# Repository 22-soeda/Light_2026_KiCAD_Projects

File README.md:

2026 ３月のROBO-ONE light 向けの回路CAD

工大祭(2025 11月頭)に向けて
 - main esp32e can
   - esp32とPCをwifiで接続して、GUIでロボットをデバッグ
   - Serial2をTTL変換して、zhコネクタで6ポート出力
   - 7.4VDCDC,12V 強電の系をまとめてスイッチング
   - canを2ポート搭載
   - 終端抵抗はブリッジで選択
   - BNO055はUART(Serial1)で実装
   - 5V reg, 3.3V DCDCを搭載
 - FSR to can
   - ATmega328P-AUをマイコンとする
   - 外部16MHz
   - FSRのシグナルをRail to Rail OPAMPで増幅、アナログ値を読み取り(4ポート)
   - MCP2515、MCP2561でcanを実装
   - 12V電源入力で、5Vregで降圧

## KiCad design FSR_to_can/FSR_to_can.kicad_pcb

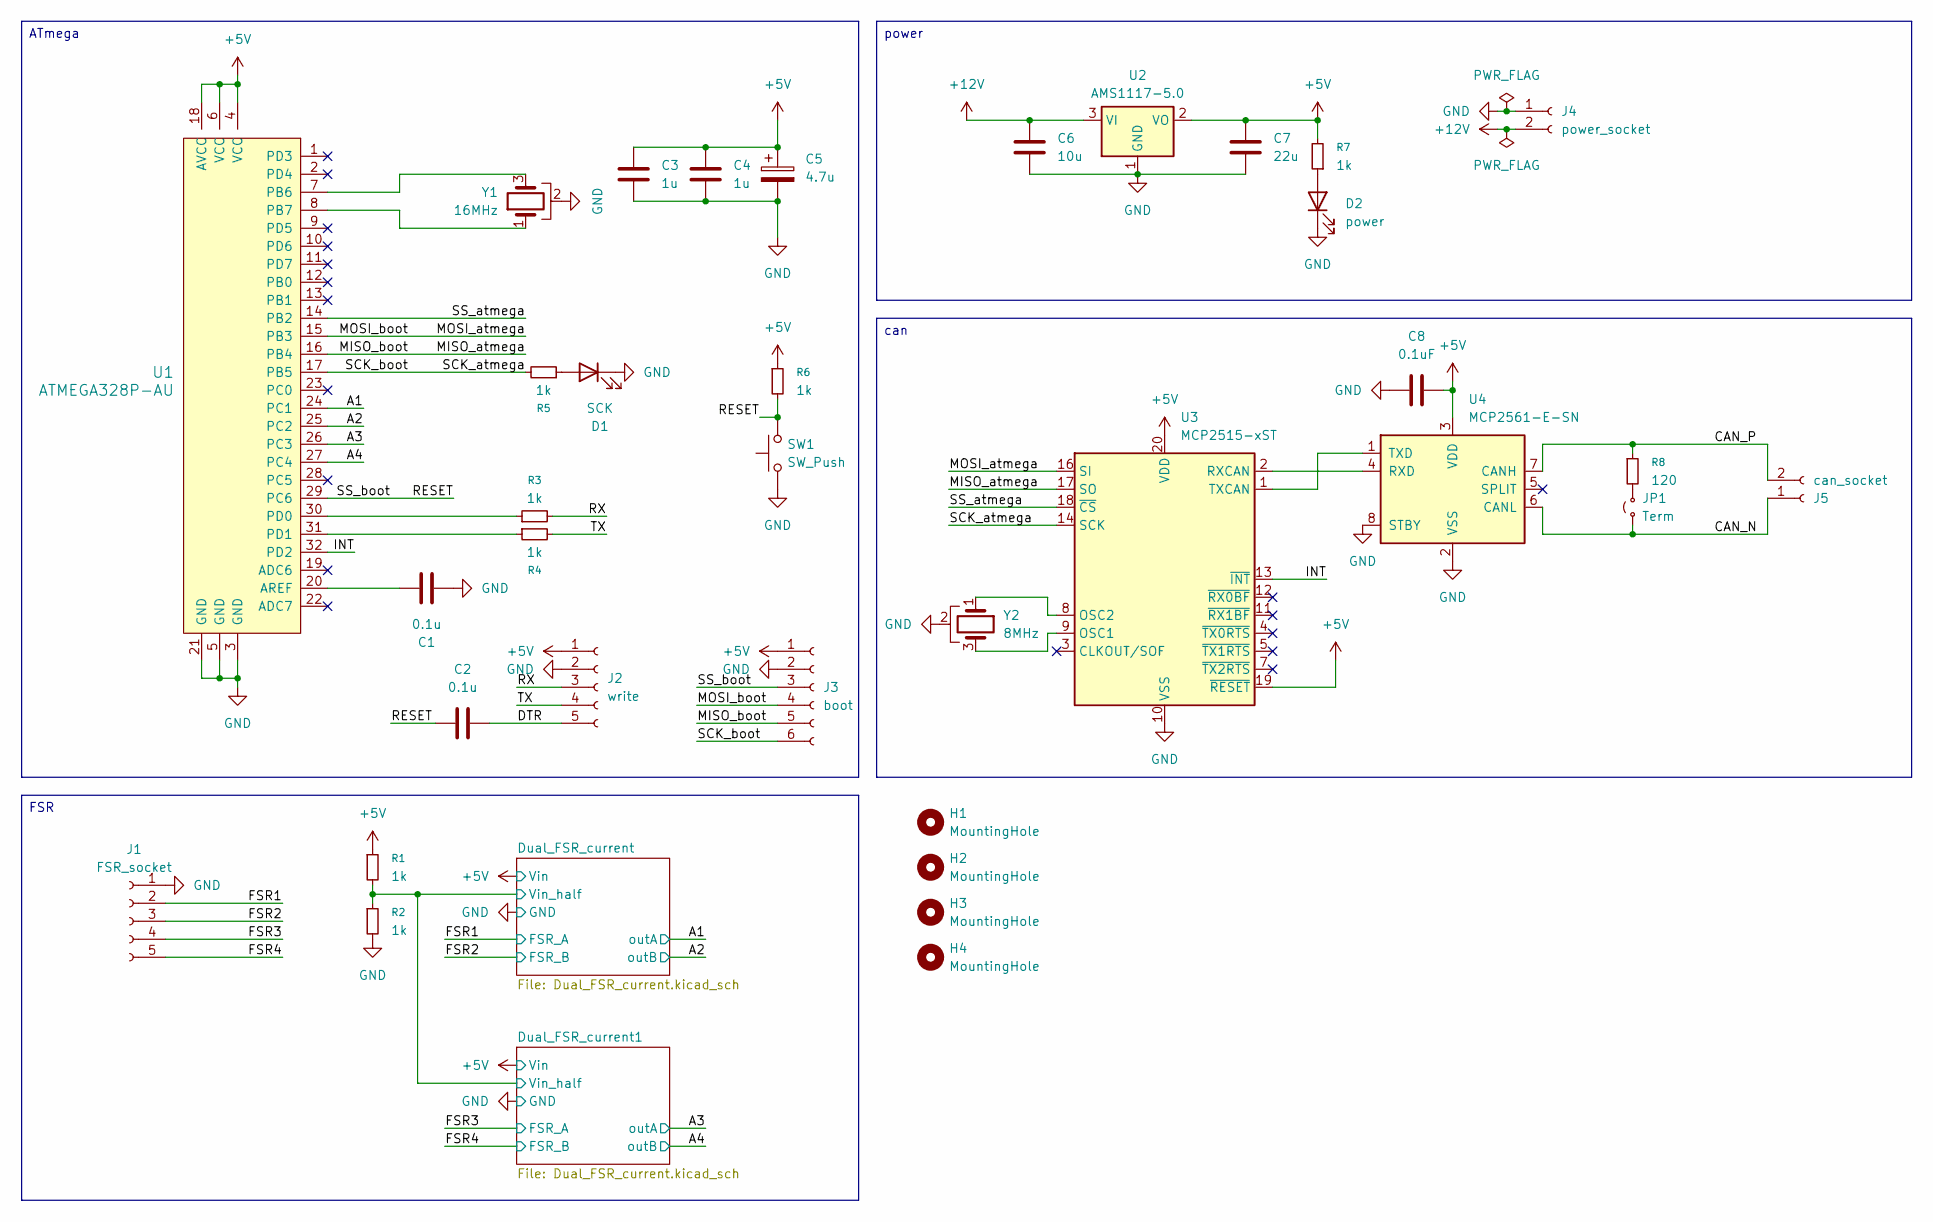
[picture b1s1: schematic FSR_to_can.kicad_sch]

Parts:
C1, C2: 0.1u; C_0805_2012Metric
C3, C4: 1u; C_0805_2012Metric
C5: 4.7u; C_0805_2012Metric
C6: 10u; C_0805_2012Metric
C7: 22u; C_0805_2012Metric
C8: 0.1uF; C_0805_2012Metric
D1: SCK; LED_0603_1608Metric_Pad1.05x0.95mm_HandSolder
D2: power; LED_0603_1608Metric_Pad1.05x0.95mm_HandSolder
H1, H2, H3, H4: MountingHole; MountingHole_2.2mm_M2_ISO14580
J1: FSR_socket; JST_ZH_S5B-ZR-SM4A-TF_1x05-1MP_P1.50mm_Horizontal
J2: write; JST_ZH_B5B-ZR_1x05_P1.50mm_Vertical
J3: boot; JST_ZH_B6B-ZR_1x06_P1.50mm_Vertical
J4: power_socket; JST_XH_S2B-XH-A_1x02_P2.50mm_Horizontal
J5: can_socket; JST_ZH_S2B-ZR-SM4A-TF_1x02-1MP_P1.50mm_Horizontal
JP1: Term; SolderJumper-2_P1.3mm_Open_RoundedPad1.0x1.5mm
R1, R2, R3, R4, R5, R6, R7: 1k; R_0603_1608Metric
R8: 120; R_0603_1608Metric
SW1: SW_Push; TVAF06-A020B-R
U1: ATMEGA328P-AU; TQFP-32_7x7mm; MPN ATMEGA328P-AU; Digi-Key_PN ATMEGA328P-AU-ND
U2: AMS1117-5.0; SOT-223-3_TabPin2
U3: MCP2515-xST; TSSOP-20_4.4x6.5mm_P0.65mm
U4: MCP2561-E-SN; SOIC-8_3.9x4.9mm_P1.27mm
Y1: 16MHz; Resonator_SMD_Murata_CSTxExxV-3Pin_3.0x1.1mm_HandSoldering
Y2: 8MHz; Resonator_SMD_Murata_CSTxExxV-3Pin_3.0x1.1mm_HandSoldering

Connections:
+5V: C3.1, C4.1, C5.1, C7.1, C8.1, J2.1, J3.1, R1.1, R6.1, R7.2, U1.4 (VCC), U1.6 (VCC), U1.18 (AVCC), U2.2 (VO), U3.19 (~RESET), U3.20 (VDD), U4.3 (VDD); also elsewhere on the board
+12V: C6.1, J4.2, U2.3 (VI)
/A1: U1.24 (PC1); also elsewhere on the board
/A2: U1.25 (PC2); also elsewhere on the board
/A3: U1.26 (PC3); also elsewhere on the board
/A4: U1.27 (PC4); also elsewhere on the board
/CAN_N: J5.1, JP1.1 (A), U4.6 (CANL)
/CAN_P: J5.2, R8.1, U4.7 (CANH)
/DTR: C2.2, J2.5
/Dual_FSR_current/Vin_half: R1.2, R2.1; also elsewhere on the board
/FSR1: J1.2; also elsewhere on the board
/FSR2: J1.3; also elsewhere on the board
/FSR3: J1.4; also elsewhere on the board
/FSR4: J1.5; also elsewhere on the board
/INT: U1.32 (PD2), U3.13 (~INT)
/MISO_atmega: J3.5, U1.16 (PB4), U3.17 (SO)
/MOSI_atmega: J3.4, U1.15 (PB3), U3.16 (SI)
/RESET: C2.1, J3.3, R6.2, SW1.2, U1.29 (PC6)
/RX: J2.3, R3.2
/SCK_atmega: J3.6, R5.2, U1.17 (PB5), U3.14 (SCK)
/SS_atmega: U1.14 (PB2), U3.18 (~CS)
/TX: J2.4, R4.2
GND: C1.2, C3.2, C4.2, C5.2, C6.2, C7.2, C8.2, D1.1 (K), D2.1 (K), J1.1, J2.2, J3.2, J4.1, R2.2, SW1.1, U1.3 (GND), U1.5 (GND), U1.21 (GND), U2.1 (GND), U3.10 (VSS), U4.2 (VSS), U4.8 (STBY), Y1.2, Y2.2; also elsewhere on the board
unnamed: D1.2 (A), R5.1
unnamed: D2.2 (A), R7.1
unnamed: JP1.2 (B), R8.2
unnamed: C1.1, U1.20 (AREF)
unnamed: U1.7 (PB6), Y1.3
unnamed: U1.8 (PB7), Y1.1
unnamed: R3.1, U1.30 (PD0)
unnamed: R4.1, U1.31 (PD1)
unnamed: U3.9 (OSC1), Y2.3
unnamed: U3.8 (OSC2), Y2.1
unnamed: U3.2 (RXCAN), U4.4 (RXD)
unnamed: U3.1 (TXCAN), U4.1 (TXD)

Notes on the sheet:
ATmega
FSR
power
can

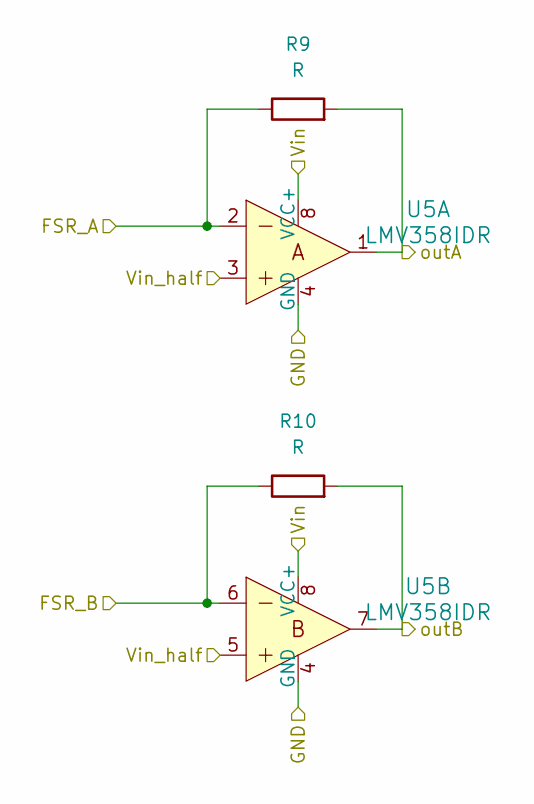
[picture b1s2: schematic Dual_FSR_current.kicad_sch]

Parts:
R9, R10: R; R_0603_1608Metric
U5: LMV358IDR; SOIC-8_W3.9mm; MPN LMV358IDR; Digi-Key_PN 296-9571-1-ND

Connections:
+5V: U5.8 (VCC+); also elsewhere on the board
/A1: R9.2, U5.1; also elsewhere on the board
/A2: R10.2, U5.7; also elsewhere on the board
/Dual_FSR_current/Vin_half: U5.3, U5.5; also elsewhere on the board
/FSR1: R9.1, U5.2; also elsewhere on the board
/FSR2: R10.1, U5.6; also elsewhere on the board
GND: U5.4 (GND); also elsewhere on the board

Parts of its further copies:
R11, R12: R; R_0603_1608Metric
U6: LMV358IDR; SOIC-8_W3.9mm; MPN LMV358IDR; Digi-Key_PN 296-9571-1-ND

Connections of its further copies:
+5V: U6.8 (VCC+); also elsewhere on the board
/A3: R11.2, U6.1; also elsewhere on the board
/A4: R12.2, U6.7; also elsewhere on the board
/Dual_FSR_current/Vin_half: U6.3, U6.5; also elsewhere on the board
/FSR3: R11.1, U6.2; also elsewhere on the board
/FSR4: R12.1, U6.6; also elsewhere on the board
GND: U6.4 (GND); also elsewhere on the board

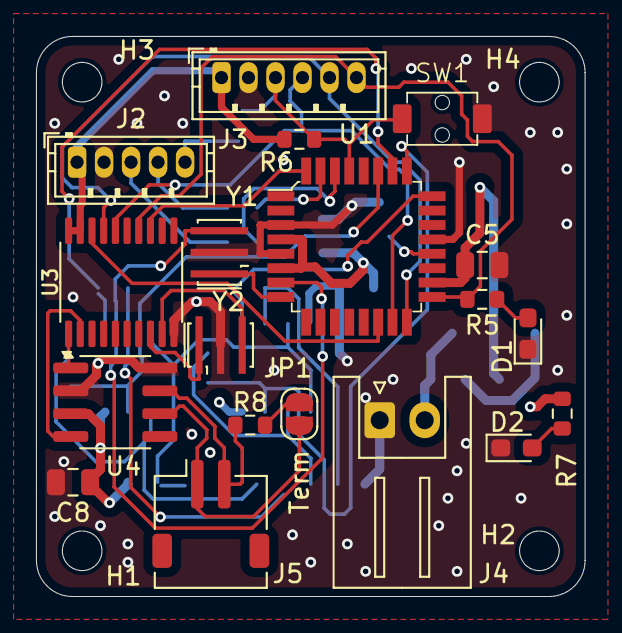
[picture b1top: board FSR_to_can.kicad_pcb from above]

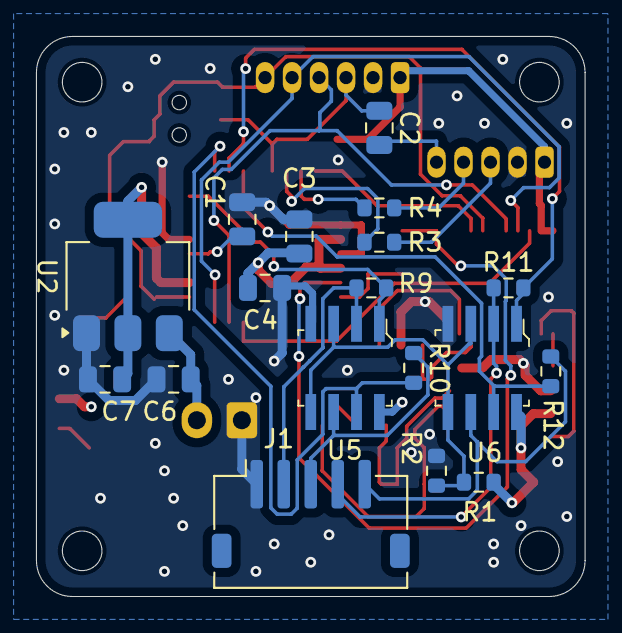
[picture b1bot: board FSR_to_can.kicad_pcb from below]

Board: 4 copper layers, 30.5 x 31.1 mm, 41 parts (18 on the bottom side), 35 nets.

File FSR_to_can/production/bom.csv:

Designator,Footprint,Quantity,Value,LCSC Part #
"C1, C2",0805,2,0.1u,
"C3, C4",0805,2,1u,
C5,0805,1,4.7u,
C6,0805,1,10u,
C7,0805,1,22u,
C8,0805,1,0.1uF,
D1,0603,1,SCK,
D2,0603,1,power,
J1,JST_ZH_S5B-ZR-SM4A-TF_1x05-1MP_P1.50mm_Horizontal,1,FSR_socket,
J2,JST_ZH_B5B-ZR_1x05_P1.50mm_Vertical,1,write,
J3,JST_ZH_B6B-ZR_1x06_P1.50mm_Vertical,1,boot,
J4,JST_XH_S2B-XH-A_1x02_P2.50mm_Horizontal,1,power_socket,
J5,JST_ZH_S2B-ZR-SM4A-TF_1x02-1MP_P1.50mm_Horizontal,1,can_socket,
JP1,SolderJumper-2_P1.3mm_Open_RoundedPad1.0x1.5mm,1,Term,
"R1, R2, R3, R4, R5, R6, R7",0603,7,1k,
"R10, R11, R12, R9",0603,4,R,
R8,0603,1,120,
SW1,TVAF06-A020B-R,1,SW_Push,
U1,TQFP-32_7x7mm,1,ATMEGA328P-AU,ATMEGA328P-AU
U2,SOT-223-3_TabPin2,1,AMS1117-5.0,
U3,TSSOP-20_4.4x6.5mm_P0.65mm,1,MCP2515-xST,
U4,SOIC-8_3.9x4.9mm_P1.27mm,1,MCP2561-E-SN,
"U5, U6",SOIC-8_W3.9mm,2,LMV358IDR,LMV358IDR
Y1,Resonator_SMD_Murata_CSTxExxV-3Pin_3.0x1.1mm_HandSoldering,1,16MHz,
Y2,Resonator_SMD_Murata_CSTxExxV-3Pin_3.0x1.1mm_HandSoldering,1,8MHz,

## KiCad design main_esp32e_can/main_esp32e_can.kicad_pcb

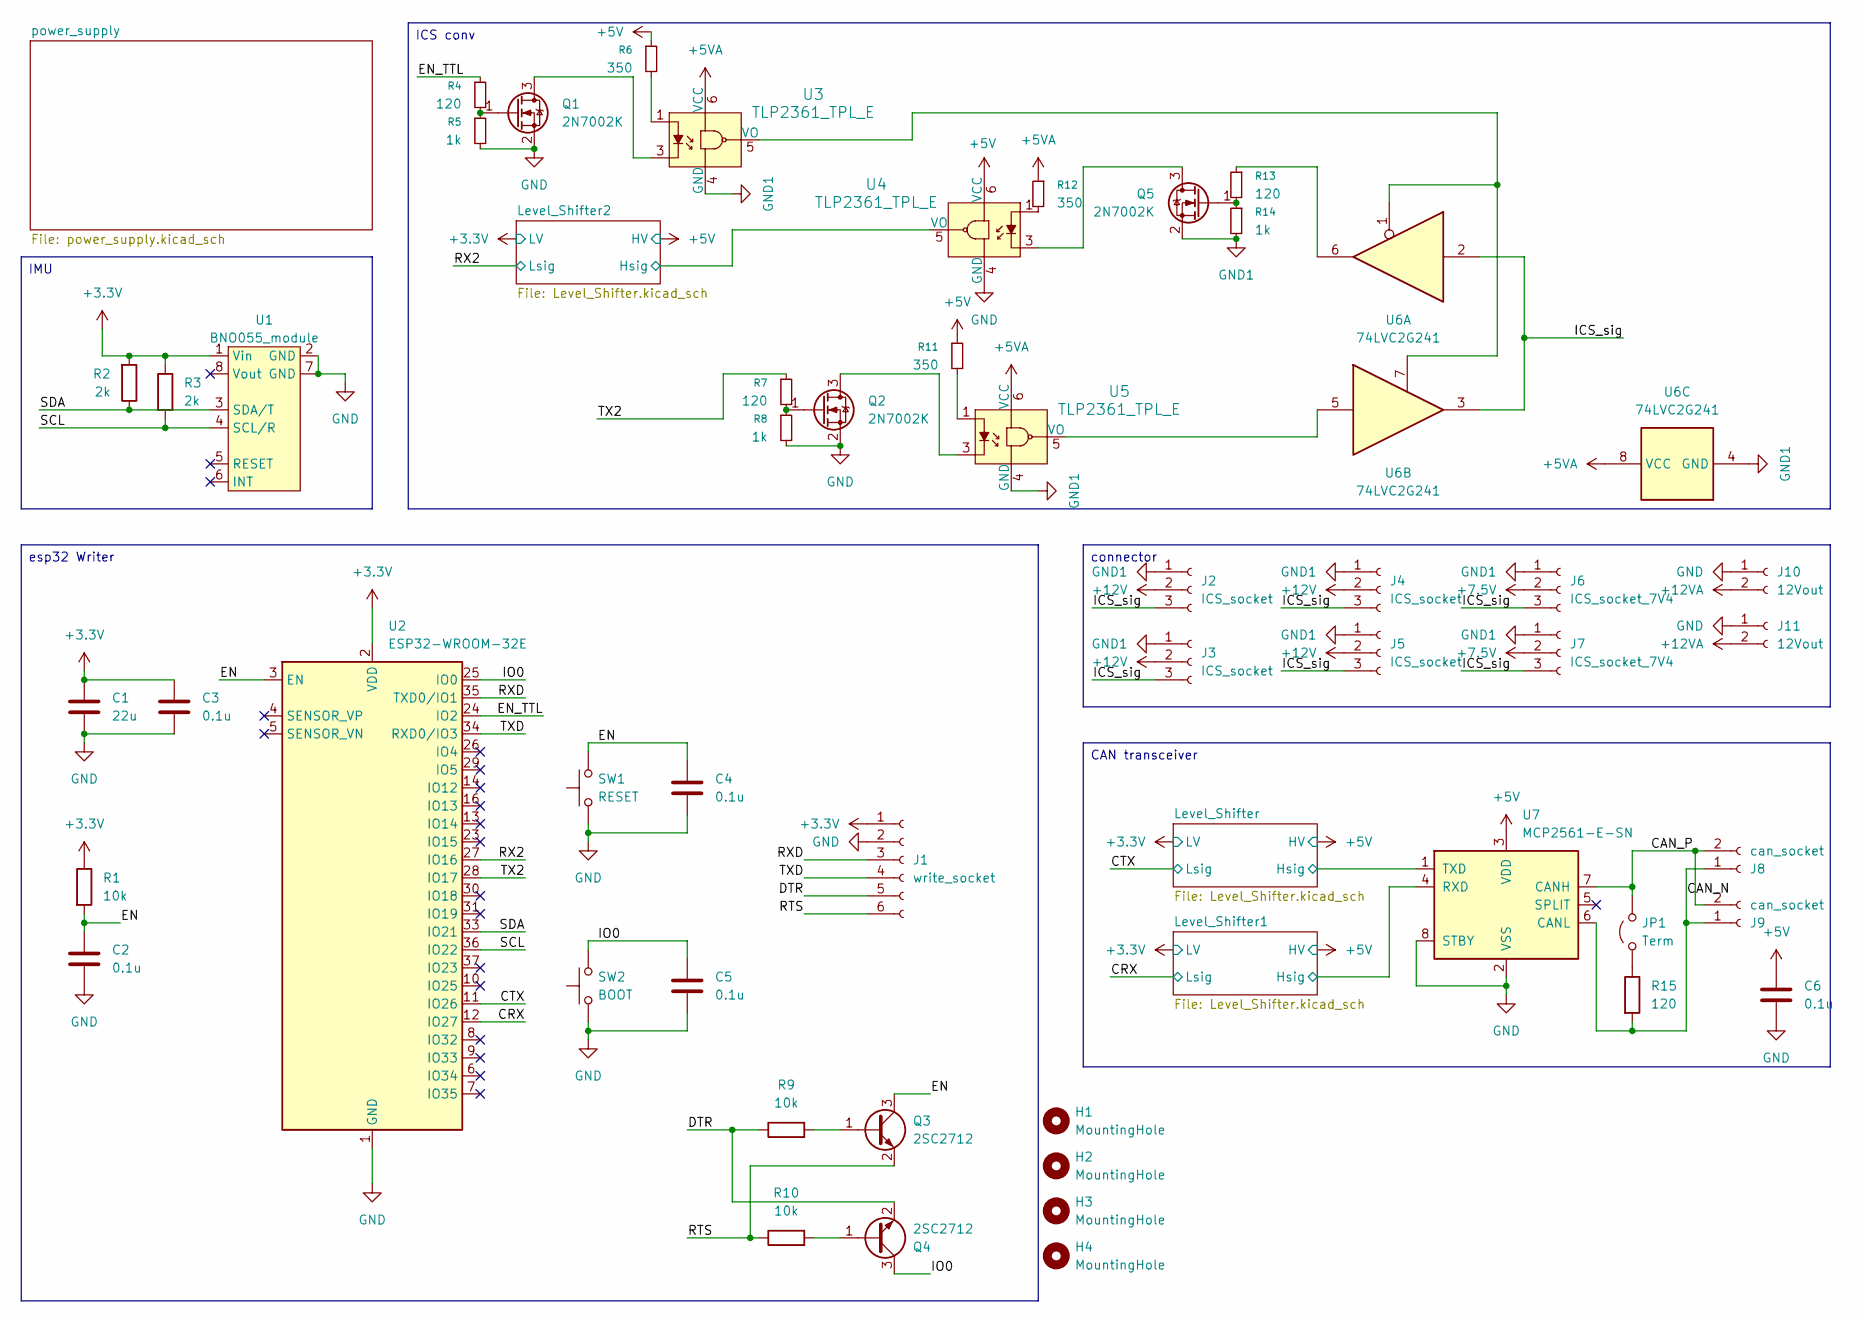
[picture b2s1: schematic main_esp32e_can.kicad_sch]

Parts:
C1: 22u; C_0805_2012Metric
C2, C3, C4, C5, C6: 0.1u; C_0805_2012Metric
H1, H2, H3, H4: MountingHole; MountingHole_3.2mm_M3
J1: write_socket; JST_ZH_B6B-ZR_1x06_P1.50mm_Vertical
J2, J3, J4, J5: ICS_socket; JST_ZH_B3B-ZR_1x03_P1.50mm_Vertical
J6, J7: ICS_socket_7V4; JST_ZH_B3B-ZR_1x03_P1.50mm_Vertical
J8, J9: can_socket; JST_ZH_B2B-ZR_1x02_P1.50mm_Vertical
J10, J11: 12Vout; JST_XA_B02B-XASK-1_1x02_P2.50mm_Vertical
JP1: Term; SolderJumper-2_P1.3mm_Open_RoundedPad1.0x1.5mm
Q1, Q2, Q5: 2N7002K; SOT-23
Q3, Q4: 2SC2712; SOT-23
R1, R9, R10: 10k; R_0603_1608Metric
R2, R3: 2k; R_0603_1608Metric
R4, R7, R13, R15: 120; R_0603_1608Metric
R5, R8, R14: 1k; R_0603_1608Metric
R6, R11, R12: 350; R_0603_1608Metric
SW1: RESET; SW_SPST_B3S-1000
SW2: BOOT; SW_SPST_B3S-1000
U1: BNO055_module
U2: ESP32-WROOM-32E; ESP32-WROOM-32D
U3, U4, U5: TLP2361_TPL_E; SOIC-6-5_W4.55mm; MPN TLP2361(TPL,E; Digi-Key_PN TLP2361(TPLECT-ND
U6: 74LVC2G241; VSSOP-8_2.3x2mm_P0.5mm
U7: MCP2561-E-SN; SOIC-8_3.9x4.9mm_P1.27mm

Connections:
+3.3V: C1.1, C3.1, J1.1, R1.1, R2.2, R3.1, U1.1 (Vin), U2.2 (VDD); also elsewhere on the board
+5V: C6.1, R6.1, R11.1, U4.6 (VCC), U7.3 (VDD); also elsewhere on the board
+5VA: R12.1, U3.6 (VCC), U5.6 (VCC), U6.8 (VCC); also elsewhere on the board
+7.5V: J6.2, J7.2; also elsewhere on the board
+12V: J2.2, J3.2, J4.2, J5.2; also elsewhere on the board
+12VA: J10.2, J11.2; also elsewhere on the board
/CAN_N: J8.1, J9.1, R15.2, U7.6 (CANL)
/CAN_P: J8.2, J9.2, JP1.2 (B), U7.7 (CANH)
/CRX: U2.12 (IO27); also elsewhere on the board
/CTX: U2.11 (IO26); also elsewhere on the board
/DTR: J1.5, Q4.2 (E), R9.1
/EN: C2.1, C4.1, Q3.3 (C), R1.2, SW1.2, U2.3 (EN)
/EN_TTL: R4.1, U2.24 (IO2)
/ICS_sig: J2.3, J3.3, J4.3, J5.3, J6.3, J7.3, U6.2, U6.3
/IO0: C5.1, Q4.3 (C), SW2.2, U2.25 (IO0)
/Level_Shifter1/Hsig: U7.4 (RXD); also elsewhere on the board
/Level_Shifter2/Hsig: U4.5 (VO); also elsewhere on the board
/Level_Shifter/Hsig: U7.1 (TXD); also elsewhere on the board
/RTS: J1.6, Q3.2 (E), R10.1
/RX2: U2.27 (IO16); also elsewhere on the board
/RXD: J1.3, U2.35 (TXD0/IO1)
/SCL: R3.2, U1.4 (SCL/R), U2.36 (IO22)
/SDA: R2.1, U1.3 (SDA/T), U2.33 (IO21)
/TX2: R7.1, U2.28 (IO17)
/TXD: J1.4, U2.34 (RXD0/IO3)
GND: C1.2, C2.2, C3.2, C4.2, C5.2, C6.2, J1.2, J10.1, J11.1, Q1.2 (S), Q2.2 (S), R5.2, R8.2, SW1.1, SW2.1, U1.2 (GND), U1.7 (GND), U2.1 (GND), U2.15 (GND), U2.38 (GND), U2.39 (GND), U4.4 (GND), U7.2 (VSS), U7.8 (STBY); also elsewhere on the board
GND1: J2.1, J3.1, J4.1, J5.1, J6.1, J7.1, Q5.2 (S), R14.2, U3.4 (GND), U5.4 (GND), U6.4 (GND); also elsewhere on the board
unnamed: JP1.1 (A), R15.1
unnamed: Q1.3 (D), U3.3
unnamed: Q1.1 (G), R4.2, R5.1
unnamed: Q2.3 (D), U5.3
unnamed: Q2.1 (G), R7.2, R8.1
unnamed: Q3.1 (B), R9.2
unnamed: Q4.1 (B), R10.2
unnamed: Q5.3 (D), U4.3
unnamed: Q5.1 (G), R13.2, R14.1
unnamed: R6.2, U3.1
unnamed: R11.2, U5.1
unnamed: R12.2, U4.1
unnamed: R13.1, U6.6
unnamed: U3.5 (VO), U6.1, U6.7
unnamed: U5.5 (VO), U6.5

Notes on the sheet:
esp32 Writer
ICS conv
CAN transceiver
IMU
connector

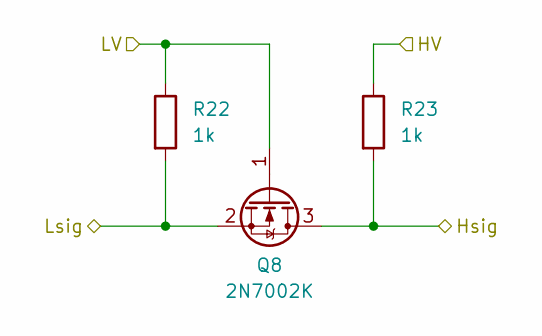
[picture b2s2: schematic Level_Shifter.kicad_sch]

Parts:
Q8: 2N7002K; SOT-23
R22, R23: 1k; R_0603_1608Metric

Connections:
+3.3V: Q8.1 (G), R22.1; also elsewhere on the board
+5V: R23.1; also elsewhere on the board
/CTX: Q8.2 (S), R22.2; also elsewhere on the board
/Level_Shifter/Hsig: Q8.3 (D), R23.2; also elsewhere on the board

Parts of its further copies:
Q9, Q10: 2N7002K; SOT-23
R24, R25, R30, R31: 1k; R_0603_1608Metric

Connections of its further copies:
+3.3V: Q9.1 (G), Q10.1 (G), R24.1, R30.1; also elsewhere on the board
+5V: R25.1, R31.1; also elsewhere on the board
/CRX: Q9.2 (S), R24.2; also elsewhere on the board
/Level_Shifter1/Hsig: Q9.3 (D), R25.2; also elsewhere on the board
/Level_Shifter2/Hsig: Q10.3 (D), R31.2; also elsewhere on the board
/RX2: Q10.2 (S), R30.2; also elsewhere on the board

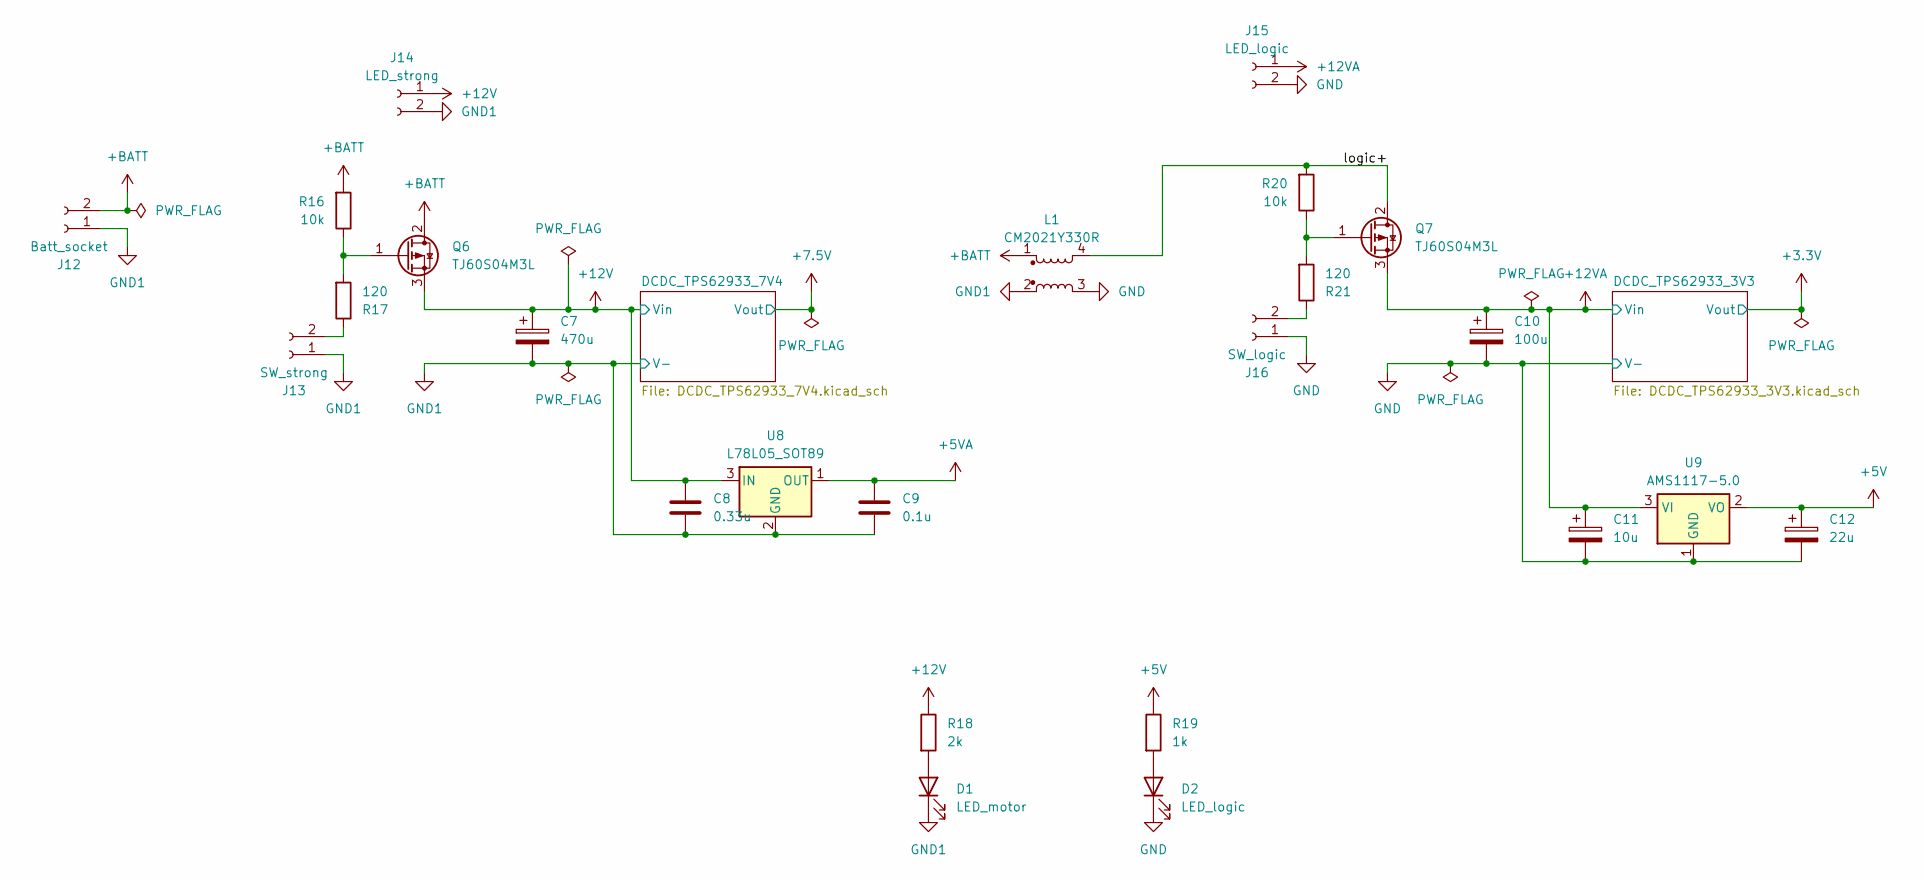
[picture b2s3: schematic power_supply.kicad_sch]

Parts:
C7: 470u; CP_Elec_10x12.6
C8: 0.33u; C_0805_2012Metric
C9: 0.1u; C_0805_2012Metric
C10: 100u; CP_Elec_6.3x5.9
C11: 10u; CP_Elec_5x5.8
C12: 22u; CP_Elec_6.3x5.9
D1: LED_motor; C_0603_1608Metric
D2: LED_logic; C_0603_1608Metric
J12: Batt_socket; AMASS_XT60-M_1x02_P7.20mm_Vertical
J13: SW_strong; JST_XA_B02B-XASK-1-A_1x02_P2.50mm_Vertical
J14: LED_strong; JST_XH_B2B-XH-AM_1x02_P2.50mm_Vertical
J15: LED_logic; JST_XH_B2B-XH-AM_1x02_P2.50mm_Vertical
J16: SW_logic; JST_XA_B02B-XASK-1-A_1x02_P2.50mm_Vertical
L1: CM2021Y330R
Q6, Q7: TJ60S04M3L; TO-252-2
R16, R20: 10k; R_0603_1608Metric
R17, R21: 120; R_0603_1608Metric
R18: 2k; R_0603_1608Metric
R19: 1k; R_0603_1608Metric
U8: L78L05_SOT89; SOT-89-3
U9: AMS1117-5.0; SOT-223-3_TabPin2

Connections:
+5V: C12.1, R19.1, U9.2 (VO); also elsewhere on the board
+5VA: C9.1, U8.1 (OUT); also elsewhere on the board
+12V: C7.1, C8.1, J14.1, Q6.3 (S), R18.1, U8.3 (IN); also elsewhere on the board
+12VA: C10.1, C11.1, J15.1, Q7.3 (S), U9.3 (VI); also elsewhere on the board
+BATT: J12.2, L1.1, Q6.2 (D), R16.2
/power_supply/logic+: L1.4, Q7.2 (D), R20.2
GND: C10.2, C11.2, C12.2, D2.1 (K), J15.2, J16.1, L1.3, U9.1 (GND); also elsewhere on the board
GND1: C7.2, C8.2, C9.2, D1.1 (K), J12.1, J13.1, J14.2, L1.2, U8.2 (GND); also elsewhere on the board
unnamed: D1.2 (A), R18.2
unnamed: D2.2 (A), R19.2
unnamed: J13.2, R17.1
unnamed: J16.2, R21.1
unnamed: Q6.1 (G), R16.1, R17.2
unnamed: Q7.1 (G), R20.1, R21.2

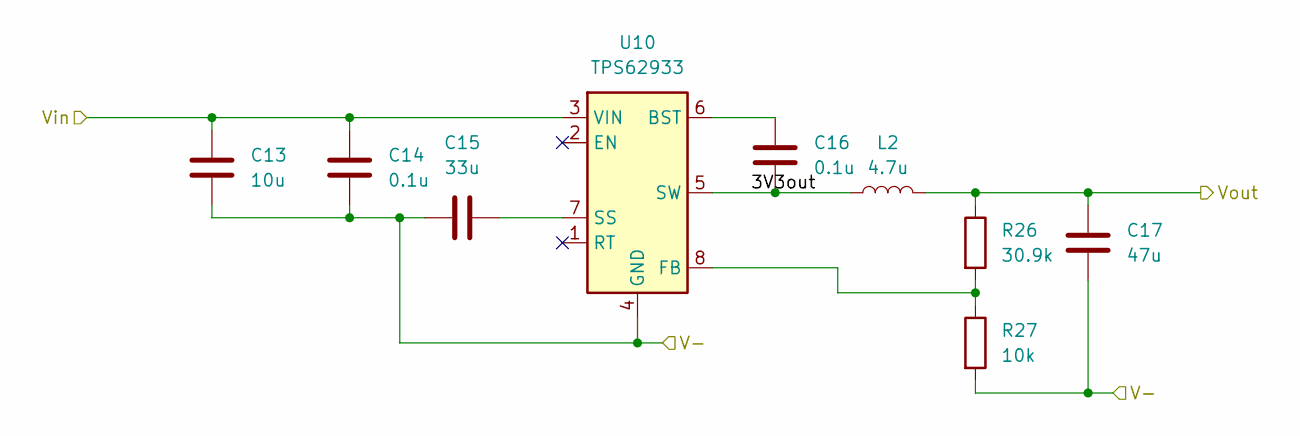
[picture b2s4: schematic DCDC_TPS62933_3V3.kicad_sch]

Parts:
C13: 10u; C_0805_2012Metric
C14, C16: 0.1u; C_0805_2012Metric
C15: 33u; C_0805_2012Metric
C17: 47u; C_0805_2012Metric
L2: 4.7u; L_Bourns-SRN8040_8x8.15mm
R26: 30.9k; R_0603_1608Metric
R27: 10k; R_0603_1608Metric
U10: TPS62933; SOT-583-8

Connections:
+3.3V: C17.1, L2.2, R26.1; also elsewhere on the board
+12VA: C13.1, C14.1, U10.3 (VIN); also elsewhere on the board
/power_supply/DCDC_TPS62933_3V3/3V3out: C16.2, L2.1, U10.5 (SW)
GND: C13.2, C14.2, C15.1, C17.2, R27.2, U10.4 (GND); also elsewhere on the board
unnamed: C16.1, U10.6 (BST)
unnamed: R26.2, R27.1, U10.8 (FB)
unnamed: C15.2, U10.7 (SS)

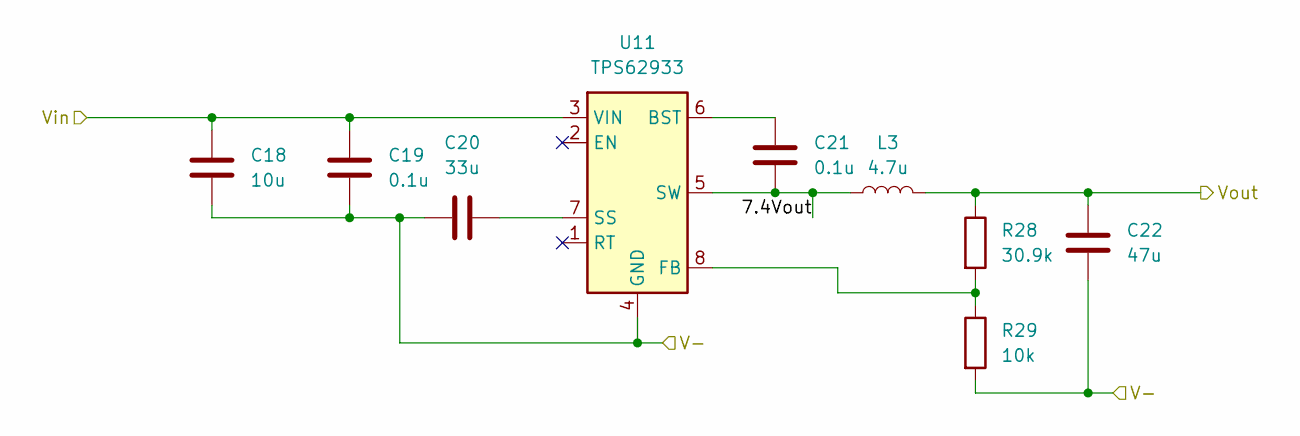
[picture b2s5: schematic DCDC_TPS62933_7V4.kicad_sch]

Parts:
C18: 10u; C_0805_2012Metric
C19, C21: 0.1u; C_0805_2012Metric
C20: 33u; C_0805_2012Metric
C22: 47u; C_0805_2012Metric
L3: 4.7u; L_Bourns-SRN8040_8x8.15mm
R28: 30.9k; R_0603_1608Metric
R29: 10k; R_0603_1608Metric
U11: TPS62933; SOT-583-8

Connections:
+7.5V: C22.1, L3.2, R28.1; also elsewhere on the board
+12V: C18.1, C19.1, U11.3 (VIN); also elsewhere on the board
/power_supply/DCDC_TPS62933_7V4/7.4Vout: C21.2, L3.1, U11.5 (SW)
GND1: C18.2, C19.2, C20.1, C22.2, R29.2, U11.4 (GND); also elsewhere on the board
unnamed: C21.1, U11.6 (BST)
unnamed: R28.2, R29.1, U11.8 (FB)
unnamed: C20.2, U11.7 (SS)

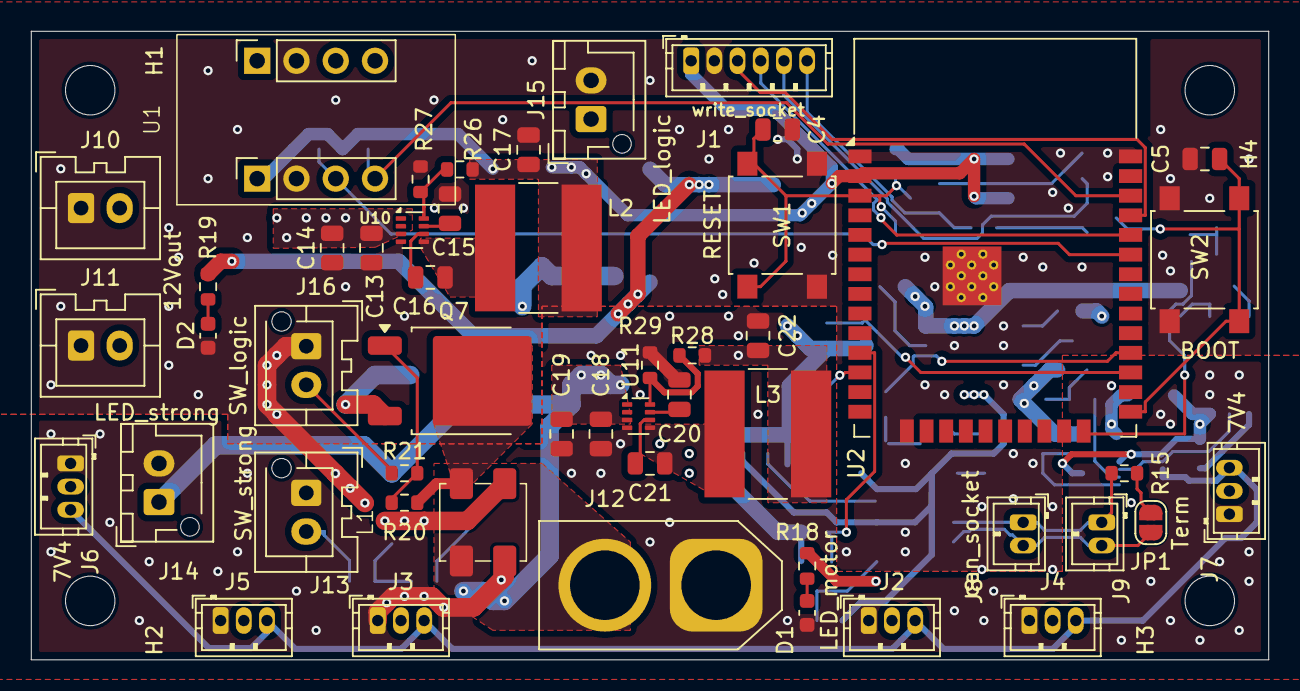
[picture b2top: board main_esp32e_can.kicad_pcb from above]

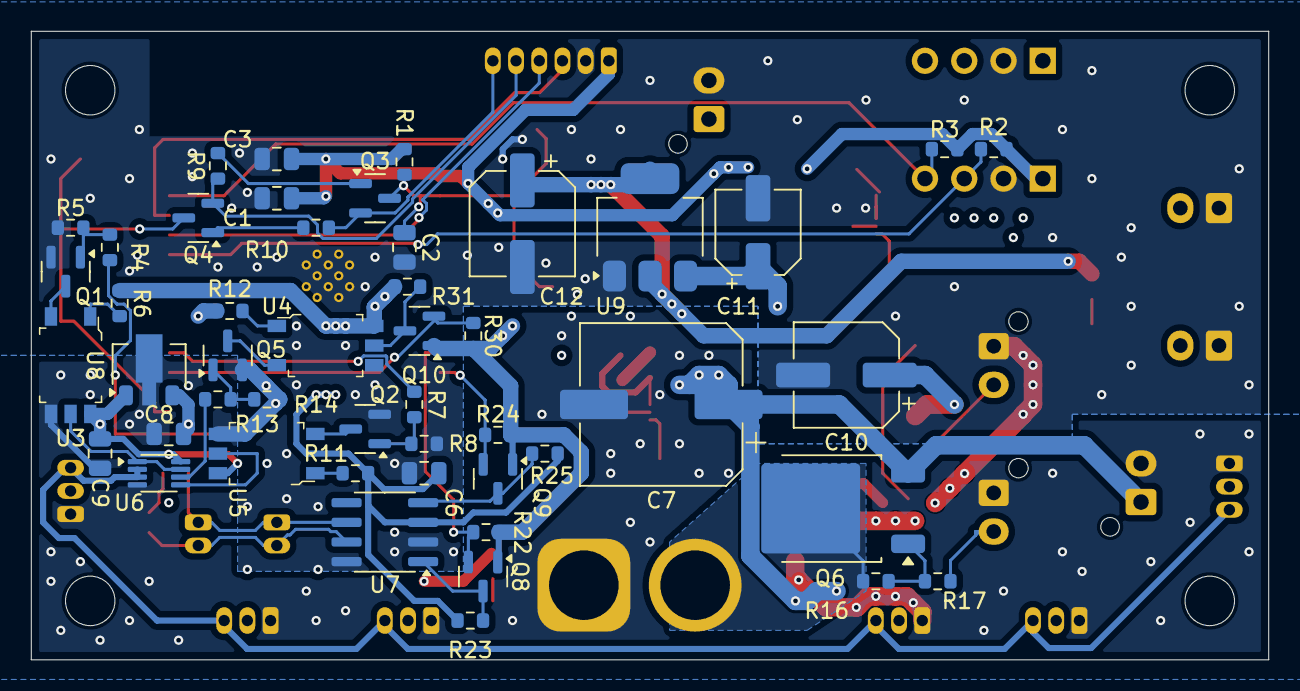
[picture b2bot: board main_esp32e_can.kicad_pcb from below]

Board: 4 copper layers, 80.0 x 40.6 mm, 102 parts (48 on the bottom side), 58 nets.

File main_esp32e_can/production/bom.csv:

Designator,Footprint,Quantity,Value,LCSC Part #
C1,0805,1,22u,
C10,CP_Elec_6.3x5.9,1,100u,
C11,CP_Elec_5x5.8,1,10u,
C12,CP_Elec_6.3x5.9,1,22u,
"C13, C18",0805,2,10u,
"C14, C16, C19, C2, C21, C3, C4, C5, C6, C9",0805,10,0.1u,
"C15, C20",0805,2,33u,
"C17, C22",0805,2,47u,
C7,CP_Elec_10x12.6,1,470u,
C8,0805,1,0.33u,
D1,0603,1,LED_motor,
D2,0603,1,LED_logic,
J1,JST_ZH_B6B-ZR_1x06_P1.50mm_Vertical,1,write_socket,
"J10, J11",JST_XA_B02B-XASK-1_1x02_P2.50mm_Vertical,2,12Vout,
J12,AMASS_XT60-M_1x02_P7.20mm_Vertical,1,Batt_socket,
J13,JST_XA_B02B-XASK-1-A_1x02_P2.50mm_Vertical,1,SW_strong,
J14,JST_XH_B2B-XH-AM_1x02_P2.50mm_Vertical,1,LED_strong,
J15,JST_XH_B2B-XH-AM_1x02_P2.50mm_Vertical,1,LED_logic,
J16,JST_XA_B02B-XASK-1-A_1x02_P2.50mm_Vertical,1,SW_logic,
"J2, J3, J4, J5",JST_ZH_B3B-ZR_1x03_P1.50mm_Vertical,4,ICS_socket,
"J6, J7",JST_ZH_B3B-ZR_1x03_P1.50mm_Vertical,2,7V4,
"J8, J9",JST_ZH_B2B-ZR_1x02_P1.50mm_Vertical,2,can_socket,
JP1,SolderJumper-2_P1.3mm_Open_RoundedPad1.0x1.5mm,1,Term,
L1,CM2021Y330R,1,CM2021Y330R,
"L2, L3",L_Bourns-SRN8040_8x8.15mm,2,4.7u,
"Q1, Q10, Q2, Q5, Q8, Q9",SOT-23,6,2N7002K,
"Q3, Q4",SOT-23,2,2SC2712,
"Q6, Q7",TO-252-2,2,TJ60S04M3L,
"R1, R10, R16, R20, R27, R29, R9",0603,7,10k,
"R11, R12, R6",0603,3,350,
"R13, R15, R17, R21, R4, R7",0603,6,120,
"R14, R19, R22, R23, R24, R25, R30, R31, R5, R8",0603,10,1k,
"R18, R2, R3",0603,3,2k,
"R26, R28",0603,2,30.9k,
SW1,SW_SPST_B3S-1000,1,RESET,
SW2,SW_SPST_B3S-1000,1,BOOT,
U1,BNO055_module,1,BNO055_module,
"U10, U11",SOT-583-8,2,TPS62933,
U2,ESP32-WROOM-32D,1,ESP32-WROOM-32E,
"U3, U4, U5",SOIC-6-5_W4.55mm,3,TLP2361_TPL_E,"TLP2361(TPL,E"
U6,VSSOP-8_2.3x2mm_P0.5mm,1,74LVC2G241,
U7,SOIC-8_3.9x4.9mm_P1.27mm,1,MCP2561-E-SN,
U8,SOT-89-3,1,L78L05_SOT89,
U9,SOT-223-3_TabPin2,1,AMS1117-5.0,

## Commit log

2025-09-27 0927_inLab
2025-09-28 0928_inhouse
2025-10-20 1st_ordered
